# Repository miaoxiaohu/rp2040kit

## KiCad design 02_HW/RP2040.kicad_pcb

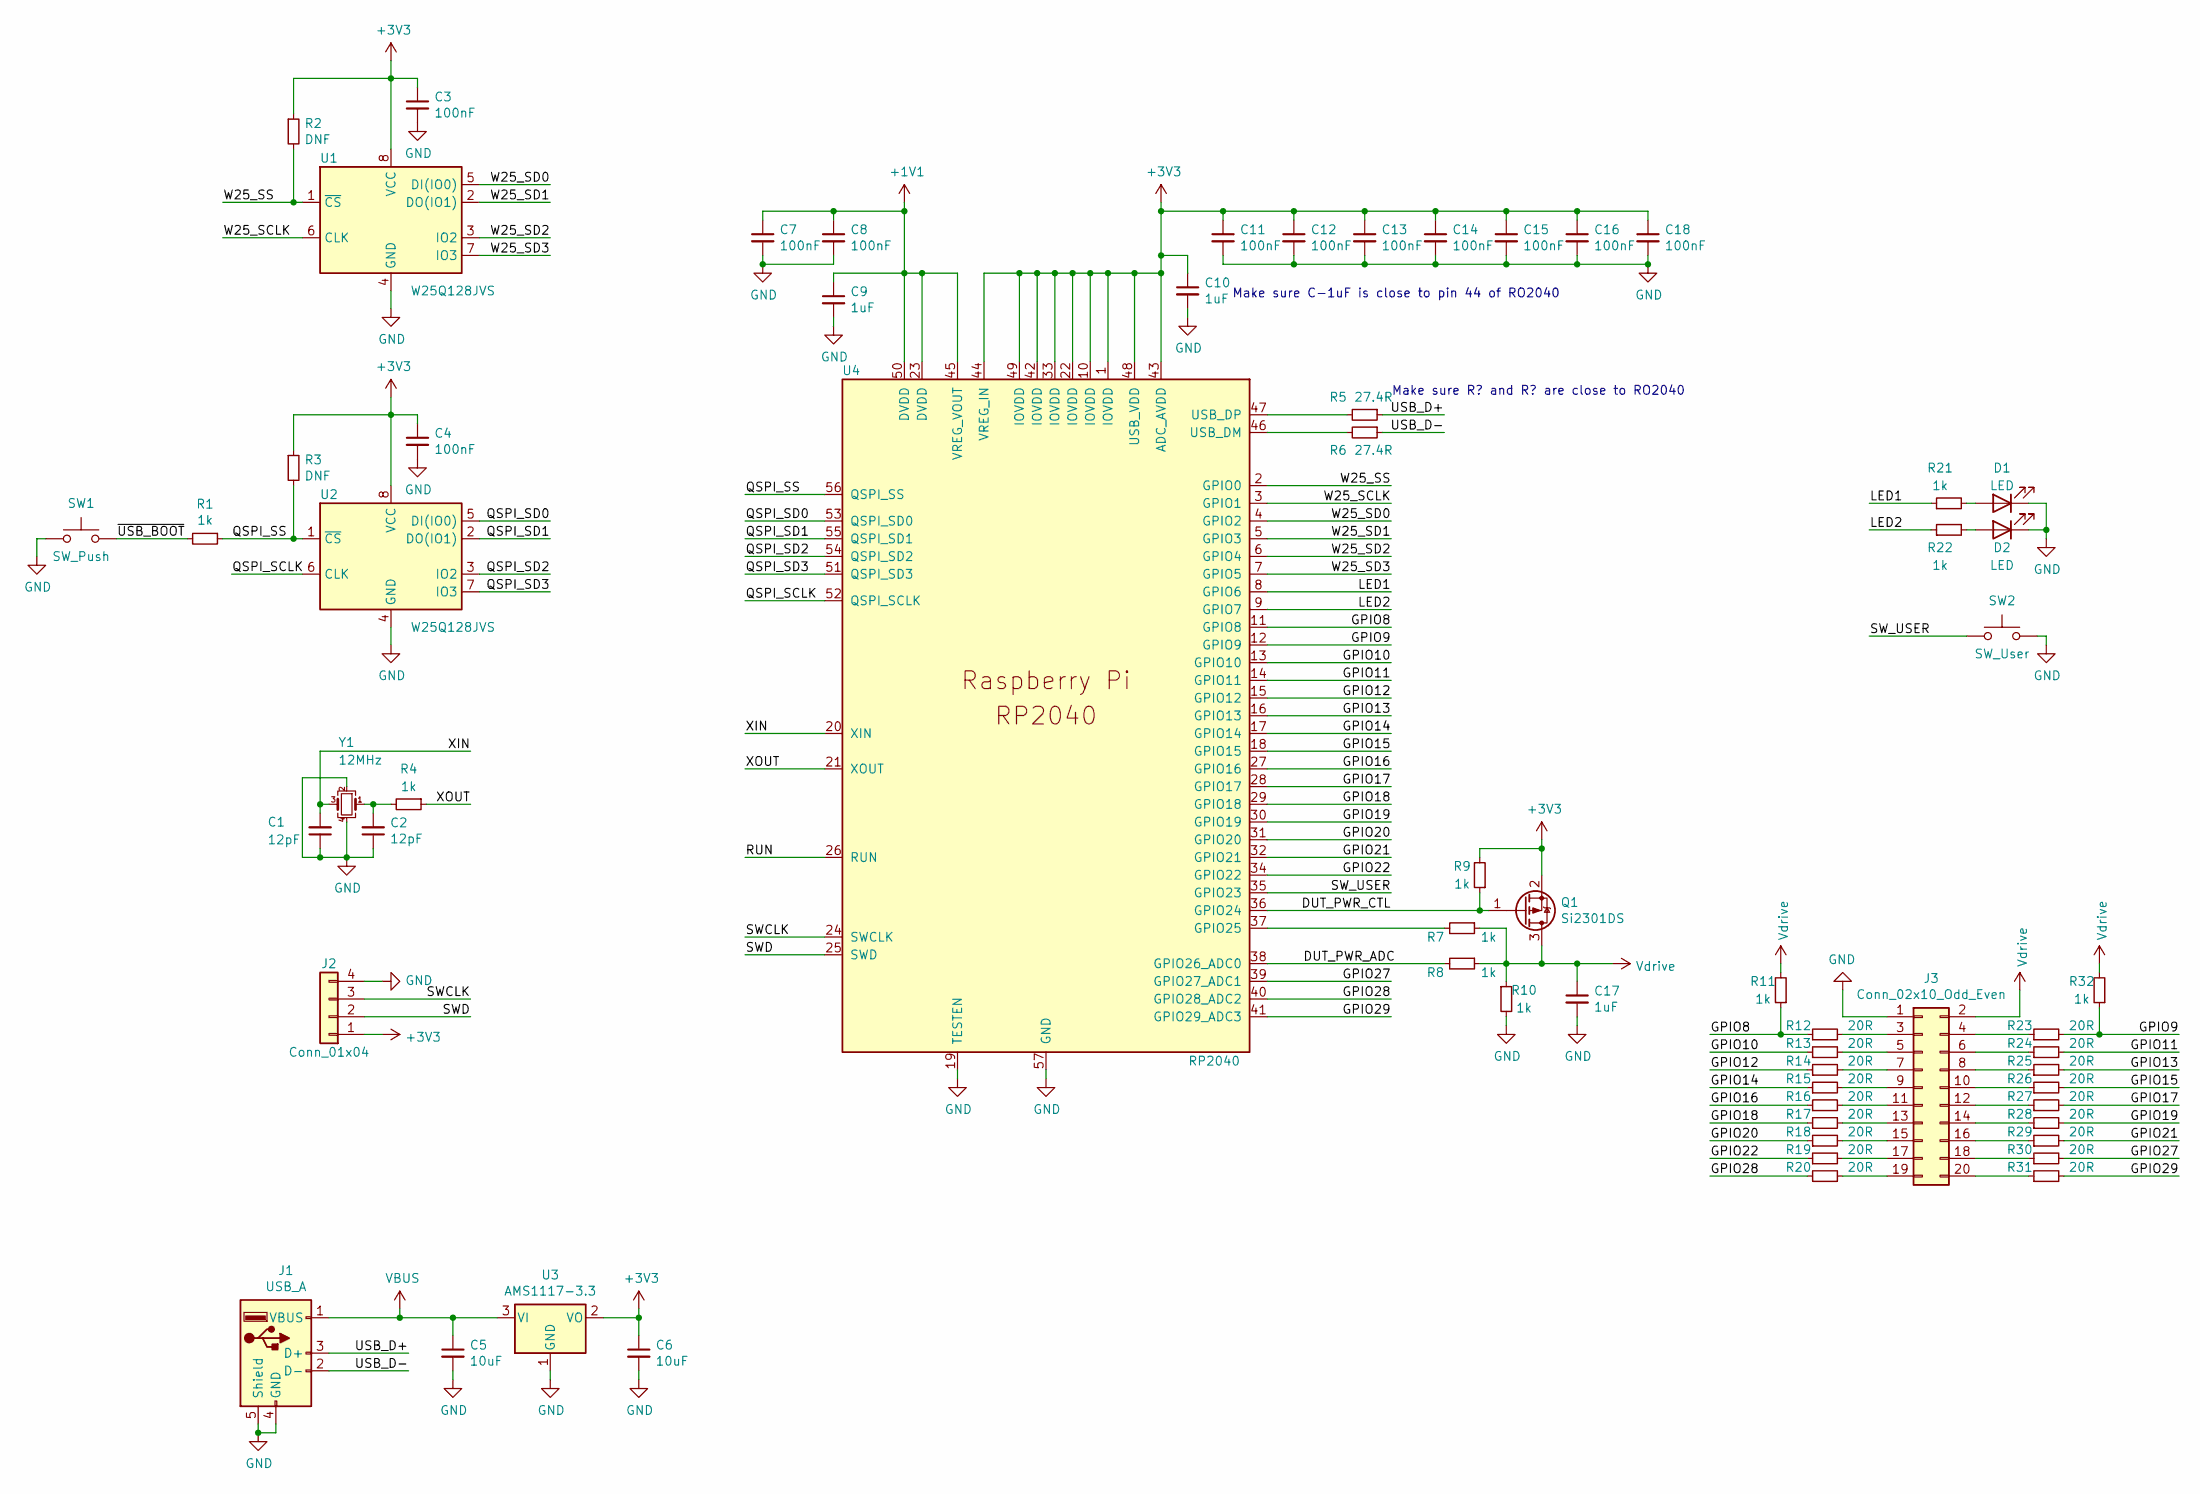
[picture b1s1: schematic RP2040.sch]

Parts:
C1, C2: 12pF; C_0201_0603Metric
C3, C4, C7, C8, C11, C12, C13, C14, C15, C16, C18: 100nF; C_0201_0603Metric
C5, C6: 10uF; C_0603_1608Metric
C9, C10, C17: 1uF; C_0402_1005Metric
D1, D2: LED; LED_0603_1608Metric
J1: USB_A; USB_A_CNCTech_1001-011-01101_Horizontal
J2: Conn_01x04; PinHeader_1x04_P2.54mm_Vertical
J3: Conn_02x10_Odd_Even; PinHeader_2x10_P2.54mm_Vertical
Q1: Si2301DS; SOT-23
R1, R4, R7, R8, R9, R10, R11, R21, R22, R32: 1k; R_0201_0603Metric
R2, R3: DNF; R_0201_0603Metric
R5, R6: 27.4R; R_0201_0603Metric
R12, R13, R14, R15, R16, R17, R18, R19, R20, R23, R24, R25, R26, R27, R28, R29, R30, R31: 20R; R_0201_0603Metric
SW1: SW_Push; SW_DIP_SPSTx01_Slide_6.7x4.1mm_W8.61mm_P2.54mm_LowProfile
SW2: SW_User; SW_DIP_SPSTx01_Slide_6.7x4.1mm_W8.61mm_P2.54mm_LowProfile
U1, U2: W25Q128JVS; SOIC-8_5.23x5.23mm_P1.27mm
U3: AMS1117-3.3; SOT-223-3_TabPin2
U4: RP2040; RP2040-QFN-56
Y1: 12MHz; Crystal_SMD_3225-4Pin_3.2x2.5mm

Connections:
+1V1: C7.1, C8.1, C9.1, U4.23 (DVDD), U4.45 (VREG_VOUT), U4.50 (DVDD)
+3V3: C3.1, C4.1, C6.1, C10.1, C11.1, C12.1, C13.1, C14.1, C15.1, C16.1, C18.1, J2.1, Q1.2 (S), R2.1, R3.1, R9.2, U1.8 (VCC), U2.8 (VCC), U3.2 (VO), U4.1 (IOVDD), U4.10 (IOVDD), U4.22 (IOVDD), U4.33 (IOVDD), U4.42 (IOVDD), U4.43 (ADC_AVDD), U4.44 (VREG_IN), U4.48 (USB_VDD), U4.49 (IOVDD)
/DUT_PWR_ADC: R8.2, U4.38 (GPIO26_ADC0)
/DUT_PWR_CTL: Q1.1 (G), R9.1, U4.36 (GPIO24)
/GPIO8: R11.1, R12.1, U4.11 (GPIO8)
/GPIO9: R23.2, R32.1, U4.12 (GPIO9)
/GPIO10: R13.1, U4.13 (GPIO10)
/GPIO11: R24.2, U4.14 (GPIO11)
/GPIO12: R14.1, U4.15 (GPIO12)
/GPIO13: R25.2, U4.16 (GPIO13)
/GPIO14: R15.1, U4.17 (GPIO14)
/GPIO15: R26.2, U4.18 (GPIO15)
/GPIO16: R16.1, U4.27 (GPIO16)
/GPIO17: R27.2, U4.28 (GPIO17)
/GPIO18: R17.1, U4.29 (GPIO18)
/GPIO19: R28.2, U4.30 (GPIO19)
/GPIO20: R18.1, U4.31 (GPIO20)
/GPIO21: R29.2, U4.32 (GPIO21)
/GPIO22: R19.1, U4.34 (GPIO22)
/GPIO27: R30.2, U4.39 (GPIO27_ADC1)
/GPIO28: R20.1, U4.40 (GPIO28_ADC2)
/GPIO29: R31.2, U4.41 (GPIO29_ADC3)
/LED1: R21.1, U4.8 (GPIO6)
/LED2: R22.1, U4.9 (GPIO7)
/QSPI_SCLK: U2.6 (CLK), U4.52 (QSPI_SCLK)
/QSPI_SD0: U2.5 (DI(IO0)), U4.53 (QSPI_SD0)
/QSPI_SD1: U2.2 (DO(IO1)), U4.55 (QSPI_SD1)
/QSPI_SD2: U2.3 (IO2), U4.54 (QSPI_SD2)
/QSPI_SD3: U2.7 (IO3), U4.51 (QSPI_SD3)
/QSPI_SS: R1.1, R3.2, U2.1 (~CS), U4.56 (QSPI_SS)
/RUN: U4.26 (RUN)
/SWCLK: J2.3, U4.24 (SWCLK)
/SWD: J2.2, U4.25 (SWD)
/SW_USER: SW2.1, U4.35 (GPIO23)
/USB_D+: J1.3 (D+), R5.1
/USB_D-: J1.2 (D-), R6.1
/W25_SCLK: U1.6 (CLK), U4.3 (GPIO1)
/W25_SD0: U1.5 (DI(IO0)), U4.4 (GPIO2)
/W25_SD1: U1.2 (DO(IO1)), U4.5 (GPIO3)
/W25_SD2: U1.3 (IO2), U4.6 (GPIO4)
/W25_SD3: U1.7 (IO3), U4.7 (GPIO5)
/W25_SS: R2.2, U1.1 (~CS), U4.2 (GPIO0)
/XIN: C1.2, U4.20 (XIN), Y1.3
/XOUT: R4.1, U4.21 (XOUT)
/~USB_BOOT: R1.2, SW1.2
GND: C1.1, C2.1, C3.2, C4.2, C5.2, C6.2, C7.2, C8.2, C9.2, C10.2, C11.2, C12.2, C13.2, C14.2, C15.2, C16.2, C17.2, C18.2, D1.1 (K), D2.1 (K), J1.4 (GND), J1.5 (Shield), J2.4, J3.1, R10.2, SW1.1, SW2.2, U1.4 (GND), U2.4 (GND), U3.1 (GND), U4.19 (TESTEN), U4.57 (GND), Y1.2, Y1.4
unnamed: C2.2, R4.2, Y1.1
unnamed: D1.2 (A), R21.2
unnamed: D2.2 (A), R22.2
unnamed: J3.3, R12.2
unnamed: J3.4, R23.1
unnamed: J3.5, R13.2
unnamed: J3.6, R24.1
unnamed: J3.7, R14.2
unnamed: J3.8, R25.1
unnamed: J3.9, R15.2
unnamed: J3.10, R26.1
unnamed: J3.11, R16.2
unnamed: J3.12, R27.1
unnamed: J3.13, R17.2
unnamed: J3.14, R28.1
unnamed: J3.15, R18.2
unnamed: J3.16, R29.1
unnamed: J3.17, R19.2
unnamed: J3.18, R30.1
unnamed: J3.19, R20.2
unnamed: J3.20, R31.1
unnamed: R5.2, U4.47 (USB_DP)
unnamed: R6.2, U4.46 (USB_DM)
unnamed: R7.2, U4.37 (GPIO25)
VBUS: C5.1, J1.1 (VBUS), U3.3 (VI)
Vdrive: C17.1, J3.2, Q1.3 (D), R7.1, R8.1, R10.1, R11.2, R32.2

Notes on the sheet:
Make sure C-1uF is close to pin 44 of RO2040
Make sure R? and R? are close to RO2040

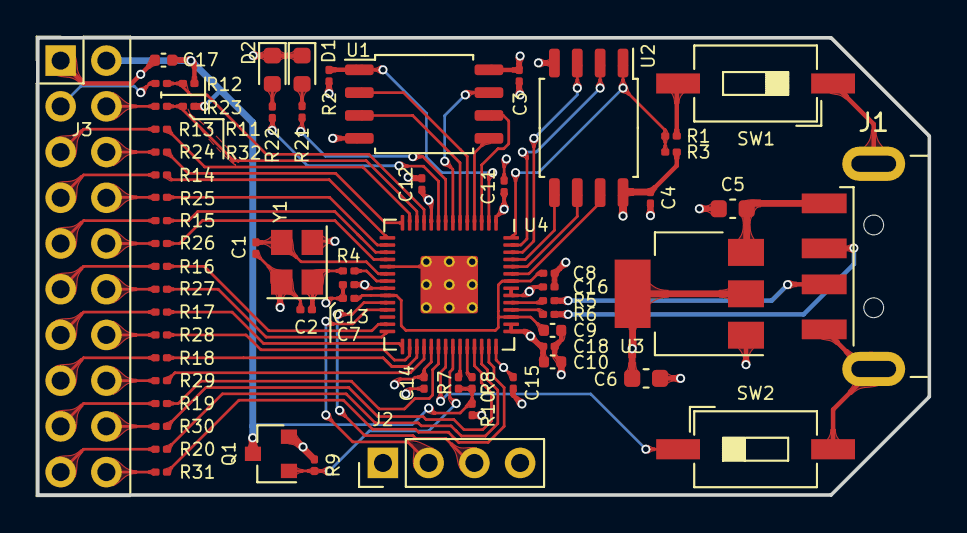
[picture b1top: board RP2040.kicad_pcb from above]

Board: 4 copper layers, 49.5 x 25.4 mm, 63 parts (0 on the bottom side), 71 nets.

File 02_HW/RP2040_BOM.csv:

"Comment","Description","Designator","Footprint","LibRef","Pins","Quantity","PartNumber","url",
"1uF","desc","C17,C10,C9,","C_0402_1005Metric","libref","2","3","","",
"12pF","desc","C2,C1,","C_0201_0603Metric","libref","4","2","","",
"10uF","desc","C6,C5,","C_0603_1608Metric","libref","2","2","","",
"100nF","desc","C8,C3,C4,C18,C16,C15,C14,C13,C12,C11,C7,","C_0201_0603Metric","libref","4","11","","",
"LED","desc","D2,D1,","LED_0603_1608Metric","libref","2","2","","",
"Si2301DS","desc","Q1,","SOT-23","libref","3","1","","",
"1k","desc","R10,R7,R32,R11,R22,R21,R9,R8,R4,R1,","R_0201_0603Metric","libref","4","10","","",
"DNF","desc","R2,R3,","R_0201_0603Metric","libref","4","2","","",
"20R","desc","R31,R30,R29,R28,R27,R26,R25,R24,R23,R20,R19,R18,R17,R16,R15,R14,R13,R12,","R_0201_0603Metric","libref","4","18","","",
"27R","desc","R6,R5,","R_0201_0603Metric","libref","4","2","","",
"SW_Push","desc","SW1,","SW_DIP_SPSTx01_Slide_6.7x4.1mm_W8.61mm_P2.54mm_LowProfile","libref","2","1","","",
"SW_User","desc","SW2,","SW_DIP_SPSTx01_Slide_6.7x4.1mm_W8.61mm_P2.54mm_LowProfile","libref","2","1","","",
"W25Q128JVS","desc","U2,U1,","SOIC-8_5.23x5.23mm_P1.27mm","libref","8","2","","",
"AMS1117-3.3","desc","U3,","SOT-223-3_TabPin2","libref","4","1","","",
"12MHz","desc","Y1,","Crystal_SMD_3225-4Pin_3.2x2.5mm","libref","4","1","","",
"Through Hole Items ",
"USB_A","desc","J1,","USB_A_CNCTech_1001-011-01101_Horizontal","libref","8","1","","",
"Conn_01x04","desc","J2,","PinHeader_1x04_P2.54mm_Vertical","libref","4","1","","",
"Conn_02x10_Odd_Even","desc","J3,","PinHeader_2x10_P2.54mm_Vertical","libref","20","1","","",
"RP2040","desc","U4,","RP2040-QFN-56","libref","70","1","","",

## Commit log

2021-09-30 上传项目文件
